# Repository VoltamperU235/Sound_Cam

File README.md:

# Sound_Cam
Sound Cam FlatBox repository

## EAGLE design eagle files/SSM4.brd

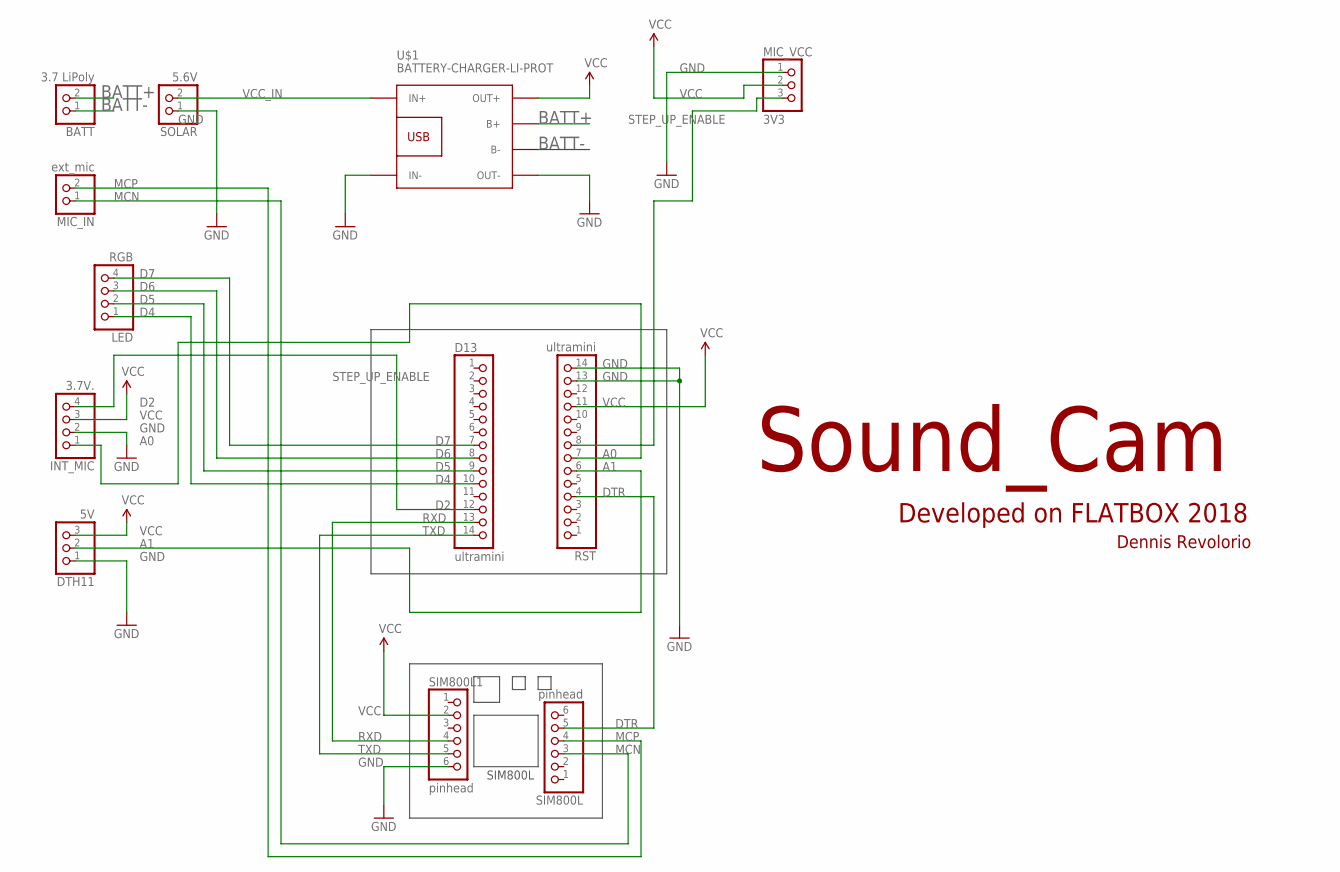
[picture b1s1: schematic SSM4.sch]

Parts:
BATT: 3.7 LiPoly; 1X02
D13: ultramini; 1X14
DTH11: 5V; 1X03
INT_MIC: 3.7V.; 1X04
LED: RGB; 1X04
MIC_IN: ext_mic; 1X02
MIC_VCC: 3V3; 1X03
RST: ultramini; 1X14
SIM800L, SIM800L1: pinhead; 1X06
SOLAR: 5.6V; 1X02
U$1: BATTERY-CHARGER-LI-PROT

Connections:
A0: INT_MIC.1, RST.7
A1: DTH11.2, RST.6
BATT+: BATT.2, U$1.B+
BATT-: BATT.1, U$1.B-
D2: D13.12, INT_MIC.4
D4: D13.10, LED.1
D5: D13.9, LED.2
D6: D13.8, LED.3
D7: D13.7, LED.4
DTR: RST.4, SIM800L.5
GND: DTH11.1, INT_MIC.2, MIC_VCC.1, RST.13, RST.14, SIM800L1.6, SOLAR.1, U$1.IN-, U$1.OUT-
MCN: MIC_IN.1, SIM800L.3
MCP: MIC_IN.2, SIM800L.4
RXD: D13.13, SIM800L1.4
STEP_UP_ENABLE: MIC_VCC.3, RST.8
TXD: D13.14, SIM800L1.5
VCC: DTH11.3, INT_MIC.3, MIC_VCC.2, RST.11, SIM800L1.2, U$1.OUT+
VCC_IN: SOLAR.2, U$1.IN+

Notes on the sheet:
SIM800L
Sound_Cam
Developed on FLATBOX 2018
Dennis Revolorio

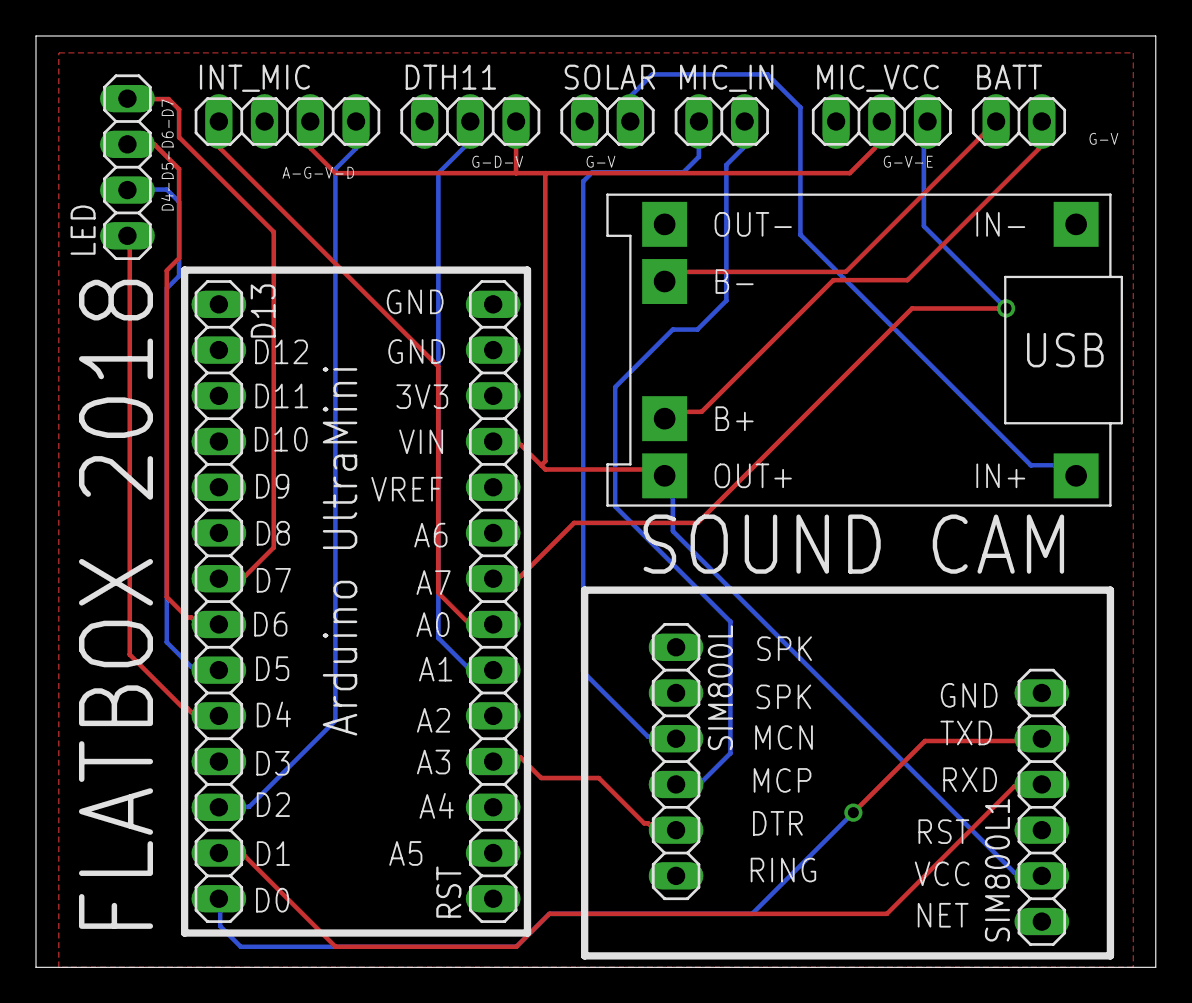
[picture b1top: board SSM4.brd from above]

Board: 2 copper layers, 62.2 x 51.7 mm, 12 parts (0 on the bottom side), 18 nets.

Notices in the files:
parts and their libraries:
diy-modules: Released under the Creative Commons Attribution 4.0 International License: http://creativecommons.org/licenses/by/4.0
SparkFun-Aesthetics: Licensing: Creative Commons ShareAlike 4.0 International - https://creativecommons.org/licenses/by-sa/4.0
